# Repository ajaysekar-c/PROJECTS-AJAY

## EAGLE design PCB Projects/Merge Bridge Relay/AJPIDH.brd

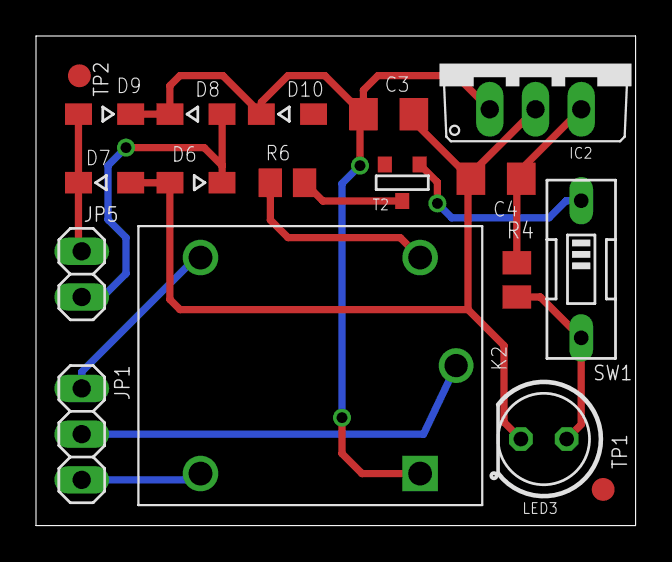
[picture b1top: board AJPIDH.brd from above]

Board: 2 copper layers, 33.3 x 27.2 mm, 18 parts (0 on the bottom side), 12 nets.

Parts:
C3: 470uF/25V; C1206
C4: 0.1uF; C1206
D6, D7, D8, D9, D10: SOD323-W
IC2: 788TV; TO220V
JP1: 1X03
JP5: 12V; 1X02
K2: SRD-05VDC-SL-C; RELAY_SRD-05VDC-SL-C
LED3: blue; LED5MM
R4: 1K; M0805
R6: 1k; M0805
SW1: EDG-01
T2: SOT-23
TP1, TP2: TPB1,27; B1,27

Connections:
ADP: C3.1, D8.C, D9.C, D10.C, IC2.1, K2.A1
GND: C3.2, C4.2, D6.A, D7.A, IC2.2, LED3.K
unnamed: K2.A2, R6.1
unnamed: SW1.1, T2.3
unnamed: R6.2, T2.1
unnamed: JP1.1, K2.NO
unnamed: JP1.2, K2.COM
unnamed: JP1.3, K2.NC
unnamed: D6.C, D8.A, JP5.1
unnamed: C4.1, IC2.3, R4.1
unnamed: D7.C, D9.A, JP5.2
PDA: LED3.A, R4.2, SW1.2

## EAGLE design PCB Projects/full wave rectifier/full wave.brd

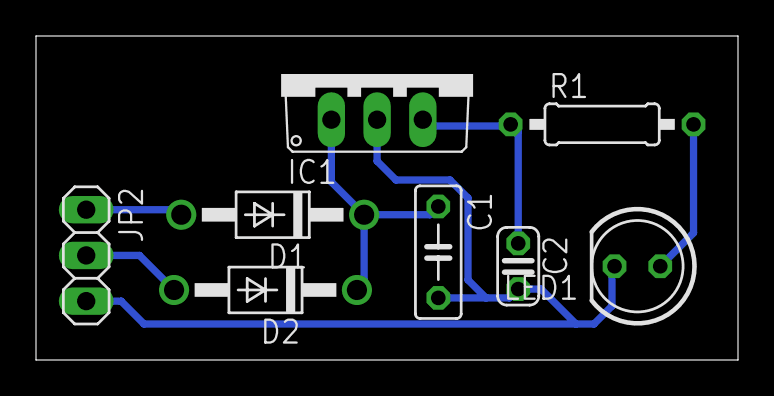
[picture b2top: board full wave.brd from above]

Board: 2 copper layers, 39.0 x 18.0 mm, 8 parts (0 on the bottom side), 6 nets.

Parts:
C1: 470uF/25v; C050-025X075
C2: 0.1uF; C025-024X044
D1, D2: 1N4004; DO41-10
IC1: 7805TV; TO220V
JP2: 12v; 1X03
LED1: blue; LED5MM
R1: 1k; 0207/10

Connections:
GND: C1.2, C2.2, IC1.2, JP2.3, LED1.K
unnamed: C1.1, D1.C, D2.C, IC1.1
unnamed: D1.A, JP2.1
unnamed: C2.1, IC1.3, R1.1
unnamed: LED1.A, R1.2
unnamed: D2.A, JP2.2
